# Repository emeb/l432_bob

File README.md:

# l432_bob
STM32L432KC6 Breakout Board

More details here: http://ebrombaugh.studionebula.com/embedded/stm32l432breakout/index.html

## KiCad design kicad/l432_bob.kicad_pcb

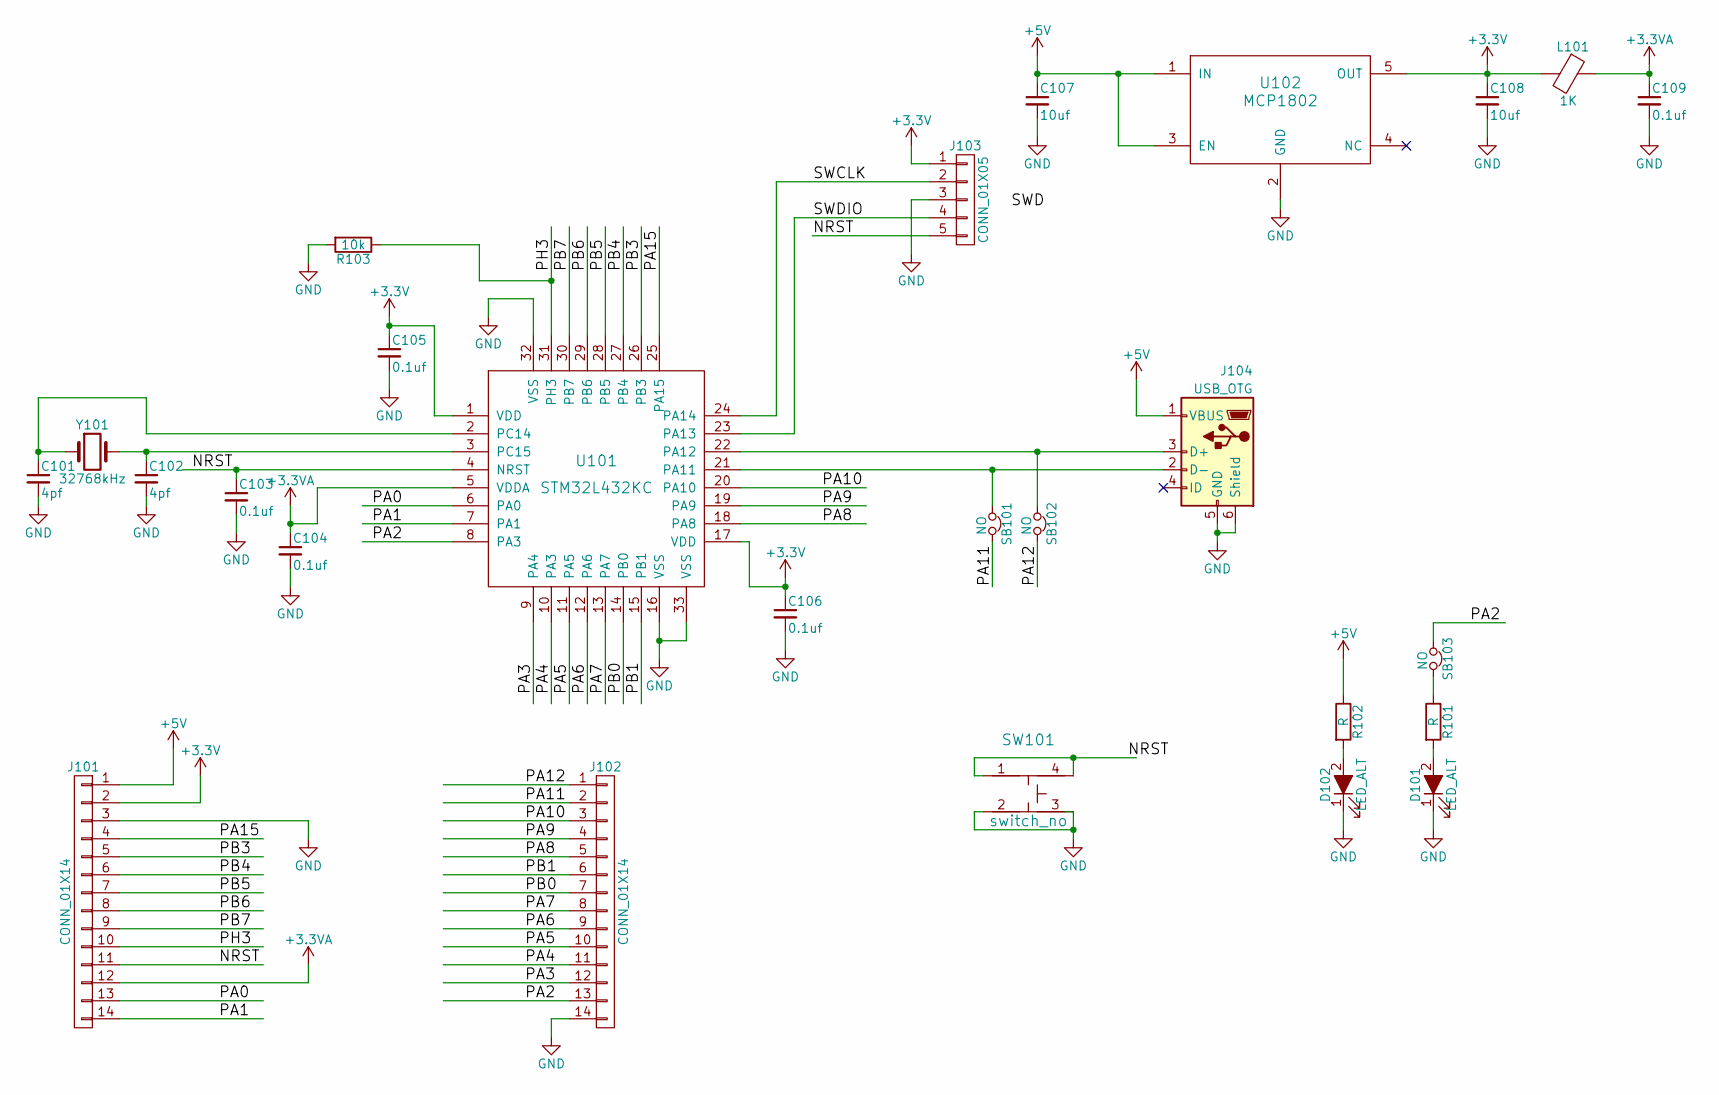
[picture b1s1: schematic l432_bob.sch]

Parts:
C101, C102: 4pf; C_0603_HandSoldering
C103, C104, C105, C106, C109: 0.1uf; C_0603_HandSoldering
C107, C108: 10uf; C_0805_HandSoldering
D101, D102: LED_ALT; LED_0603_HandSoldering
J101, J102: CONN_01X14; Pin_Header_Straight_1x14_Pitch2.54mm
J103: CONN_01X05; Pin_Header_Straight_1x05_Pitch2.54mm
J104: USB_OTG; USB_Micro-B_10103594-0001LF_NoSlot
L101: 1K; R_0603_HandSoldering
R101, R102: R; R_0603_HandSoldering
R103: 10k; R_0603_HandSoldering
SB101, SB102, SB103: NO; JUMPER-SOLDER-SMD
SW101: switch_no; PUSHBUTTON_SMD_KMR2
U101: STM32L432KC; QFN-32-1EP_5x5mm_Pitch0.5mm_extended_pad
U102: MCP1802; SOT-23-5_HandSoldering
Y101: 32768kHz; NX3215SA_XTAL

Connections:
+3.3VA: C104.1, C109.1, J101.12, L101.1, U101.5 (VDDA)
+3V3: C105.1, C106.1, C108.1, J101.2, J103.1, L101.2, U101.1 (VDD), U101.17 (VDD), U102.5 (OUT)
+5V: C107.1, J101.1, J104.1 (VBUS), R102.1, U102.1 (IN), U102.3 (EN)
/NRST: C103.1, J101.11, J103.5, SW101.1, SW101.4, U101.4 (NRST)
/PA0: J101.13, U101.6 (PA0)
/PA1: J101.14, U101.7 (PA1)
/PA2: J102.13, SB103.1, U101.8 (PA3)
/PA3: J102.12, U101.9 (PA4)
/PA4: J102.11, U101.10 (PA3)
/PA5: J102.10, U101.11 (PA5)
/PA6: J102.9, U101.12 (PA6)
/PA7: J102.8, U101.13 (PA7)
/PA8: J102.5, U101.18 (PA8)
/PA9: J102.4, U101.19 (PA9)
/PA10: J102.3, U101.20 (PA10)
/PA11: J102.2, SB101.2
/PA12: J102.1, SB102.2
/PA15: J101.4, U101.25 (PA15)
/PB0: J102.7, U101.14 (PB0)
/PB1: J102.6, U101.15 (PB1)
/PB3: J101.5, U101.26 (PB3)
/PB4: J101.6, U101.27 (PB4)
/PB5: J101.7, U101.28 (PB5)
/PB6: J101.8, U101.29 (PB6)
/PB7: J101.9, U101.30 (PB7)
/PH3: J101.10, R103.1, U101.31 (PH3)
/SWCLK: J103.2, U101.24 (PA14)
/SWDIO: J103.4, U101.23 (PA13)
GND: C101.2, C102.2, C103.2, C104.2, C105.2, C106.2, C107.2, C108.2, C109.2, D101.1 (K), D102.1 (K), J101.3, J102.14, J103.3, J104.5 (GND), J104.6 (Shield), R103.2, SW101.2, SW101.3, U101.16 (VSS), U101.32 (VSS), U101.33 (VSS), U102.2 (GND)
unnamed: C101.1, U101.2 (PC14), Y101.1
unnamed: C102.1, U101.3 (PC15), Y101.2
unnamed: D101.2 (A), R101.2
unnamed: D102.2 (A), R102.2
unnamed: J104.2 (D-), SB101.1, U101.21 (PA11)
unnamed: J104.3 (D+), SB102.1, U101.22 (PA12)
unnamed: R101.1, SB103.2

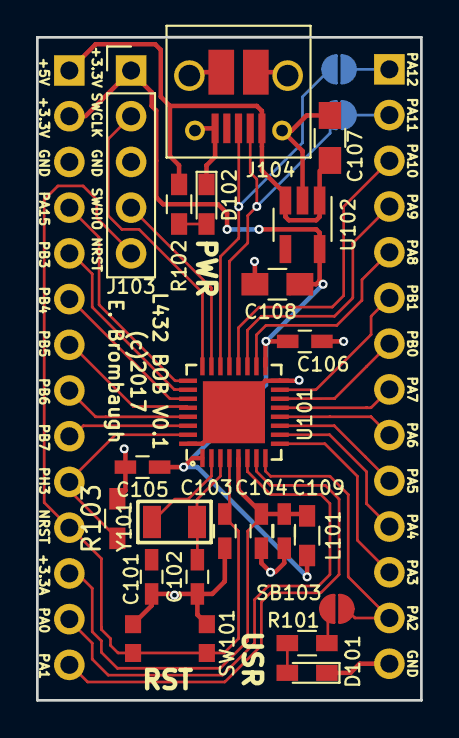
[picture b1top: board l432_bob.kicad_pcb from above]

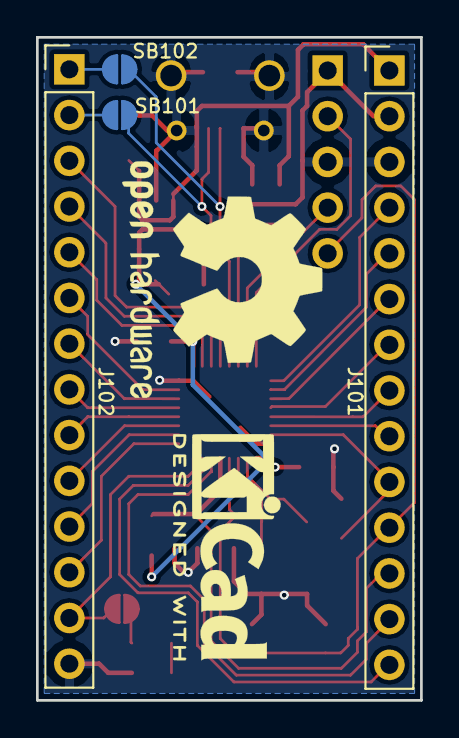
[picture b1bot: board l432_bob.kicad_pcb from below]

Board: 2 copper layers, 21.3 x 36.8 mm, 26 parts (4 on the bottom side), 36 nets.

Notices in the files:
kicad/l432_bob.kicad_pcb:
(c)2017
